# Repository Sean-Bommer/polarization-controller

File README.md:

# polarization-controller-Unit
Repository for all the final files of the polarization controller project completed by Sean Bommer.

The polarization controller unit (PCU) is a modular laser cut device that is capable of rotating 2 1-inch polarizing waveplates.
it operates using an Arduino Nano and two DRV8834 stepper motor drivers, found at the folowing link.
https://www.pololu.com/product/2134
which control 2 28BYJ-48 5V Stepper Motors.
the construction is made up from 3mm acrylic and M3 bolts and nuts.

The PCU can be powered from the 5V line of the Arduino Nano, which allowing for the whole system to be run from the USB port of a PC.
The OS for the device is contained in the Arduino IDE code in this repository, two versions are available:
  
  The 'position' version sets the start location (it's position when switched on) as position = 0 Degrees and then rotates the waveplate     to  the target orientation with respect to this 0 position. For example, upon start up the device is asked to rotate to 90 degrees. the   device turns to this position. it is then asked to turn to 90 degrees again. the device does not move, as it is already at 90 degrees.
  
  The 'distance' version reads the degrees input as how far it should rotate. For example, upon start up the device is asked to rotate 90   degrees. the device turns this distance. it is then asked to turn 90 degrees again. the device will turn another 90 degrees, thus being   180 degrees from it's origin point.
  
This device is designed to be very modular, and complies to the dimensions required for the Thorlabs cage mount system. the waveplates are controlled independently of each other so it can operate with either one or 2 waveplates. 

When attached to the base mount via the M3 screws the, the whole system can be mounted to an optical breadboard via the 2 slots either side of the base and up to 4 L-shaped mounting brackets. In this configuration, with two waveplates setup, the PCU can serve as a mounting point for a simple optical cage setup as well.

FOLDERS:
        
        The Arduino folder contains the position and distance versions of the OS which are compatible with the arduino Nano.
        it also contains the autostep testscript, that can be used to check if all components work without serial communication and also 
        measure any motor drift the system has when used in conjunction with the Matlab findMotorDrift.m file.
        
        The Matlab folder has the findMotorDrift.m file which can be used to measure the motor drift of the system whn used with the
        autostep arduino script.
        
        The LabVIEW folder holds a simple Serial Interface with the PCU allowing simple click and go operation of the PCU

        The PCB folder has all the Kicad files needed for the design of the PCU PCB on a one-sided copper plate.

        the Fusion 360 contains the design files for the laser cut acrylic parts of the PCU.

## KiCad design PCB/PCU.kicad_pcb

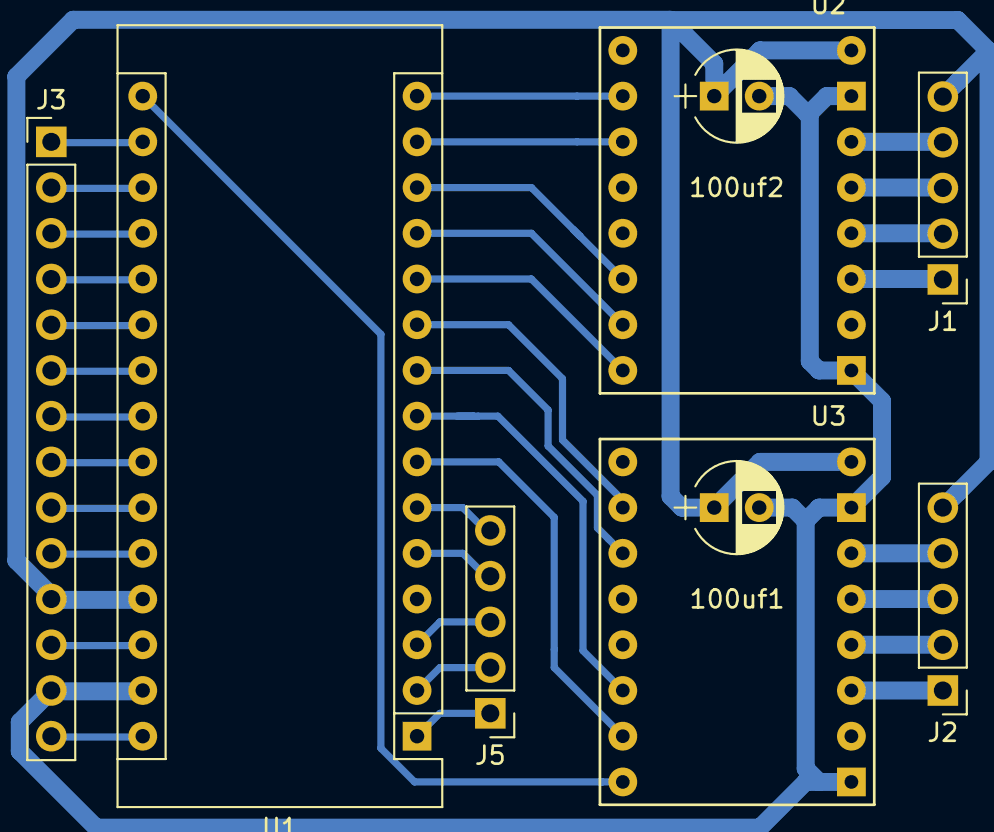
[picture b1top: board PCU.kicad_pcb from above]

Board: 2 copper layers, 9 parts (0 on the bottom side), 37 nets.

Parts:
100uf1, 100uf2: CP1; CP_Radial_D5.0mm_P2.50mm
J1, J2, J5: Conn_01x05_Male; Pin_Header_Straight_1x05_Pitch2.54mm
J3: Conn_01x14_Male; Pin_Header_Straight_1x14_Pitch2.54mm
U1: ArduinoNano; Arduino_Nano
U2, U3: DRV8834_LV; drv8834

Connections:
/VMOT: 100uf1.1, 100uf2.1, J1.5, J2.5, J3.11, U1.27, U2.16, U3.16
GND: 100uf1.2, 100uf2.2, J3.13, U1.29, U2.9, U2.15, U3.9, U3.15
unnamed: J1.1, U2.11
unnamed: J1.2, U2.12
unnamed: J1.3, U2.13
unnamed: J1.4, U2.14
unnamed: J2.1, U3.11
unnamed: J2.2, U3.12
unnamed: J2.3, U3.13
unnamed: J2.4, U3.14
unnamed: J3.1, U1.17
unnamed: J3.2, U1.18
unnamed: J3.3, U1.19
unnamed: J3.4, U1.20
unnamed: J3.5, U1.21
unnamed: J3.6, U1.22
unnamed: J3.7, U1.23
unnamed: J3.8, U1.24
unnamed: J3.9, U1.25
unnamed: J3.10, U1.26
unnamed: J3.12, U1.28
unnamed: J3.14, U1.30
unnamed: J5.1, U1.1
unnamed: J5.2, U1.2
unnamed: J5.3, U1.3
unnamed: J5.4, U1.5
unnamed: J5.5, U1.6
unnamed: U1.7, U3.7
unnamed: U1.8, U3.6
unnamed: U1.9, U3.3
unnamed: U1.10, U3.2
unnamed: U1.11, U2.8
unnamed: U1.12, U2.7
unnamed: U1.13, U2.6
unnamed: U1.14, U2.3
unnamed: U1.15, U2.2
unnamed: U1.16, U3.8

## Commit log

2018-08-20 Add files via upload
    Arduino based OS code for the polarisation controller
2018-09-04 Add files via upload
    Only the relevant KiCad files
